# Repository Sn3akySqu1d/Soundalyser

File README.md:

# Description  
Soundalyser is a compact portable sound monitoring device that records, logs and displays ambient noise.  

Key Features:  
5 screens navigatable using a rotary encoder:  
Waveform, sound bar chart, mood screen that compares the current average sound levels to recommended limits, a stats screen that shows number of samples taken, minimum/maximum recorded sound levels and average sound level and a screen that shows details about the SD card.

Data is logged to a csv file on an SD card every 10 minuites so that it can be saved and analysed later. A sample is taken once a second.

A buzzer beeps to alert the user if the sound level gets dangerously loud. (>900 average)

Display autosleeps and is woken by pushing in the rotary encoder.  

I made this project as an easy way to tell if the environment is too loud.

# BOM 
| Component                                       | Link                                                                                                                                               | Price (USD) |
| ----------------------------------------------- | -------------------------------------------------------------------------------------------------------------------------------------------------- | ----------- |
| 0.96 Inch OLED Display Module (SSD1306)         | [https://www.aliexpress.com/item/1005006262908701.html](https://www.aliexpress.com/item/1005006262908701.html)                                     | 3.51        |
| GY-MAX4466 Electret Microphone Amplifier Module | [https://www.aliexpress.com/item/1005006070858246.html](https://www.aliexpress.com/item/1005006070858246.html)                                     | 3.92        |
| RP2040 Seeed XIAO                               | [https://www.aliexpress.com/item/1005003682505451.html](https://www.aliexpress.com/item/1005003682505451.html)                                     | 12.11       |
| Rotary Encoder                                  | [https://www.aliexpress.com/item/1975155185.html](https://www.aliexpress.com/item/1975155185.html)                                                 | 3.62        |
| Buzzer                                          | [https://www.aliexpress.com/item/1005004883467830.html#nav-specification](https://www.aliexpress.com/item/1005004883467830.html#nav-specification) | 3.43        |
| MicroSD Card Reader                             | [https://www.aliexpress.com/item/1005006248599786.html](https://www.aliexpress.com/item/1005006248599786.html)                                     | 2.39        |
| MicroSD Card                                    | [https://www.aliexpress.com/item/1005007118463161.html](https://www.aliexpress.com/item/1005007118463161.html)                                     | 1.99        |
| M3 Screws                                       | [https://www.aliexpress.com/item/32950591394.html](https://www.aliexpress.com/item/32950591394.html)                                               | 4.89        |
| PCB (custom)                                    | [https://jlcpcb.com](https://jlcpcb.com)                                                                                                           | 1.50        |
| Case                                            | Printed with my own 3D printer                                                                                                                     | 0.00        |
 Total: 37.36 usd

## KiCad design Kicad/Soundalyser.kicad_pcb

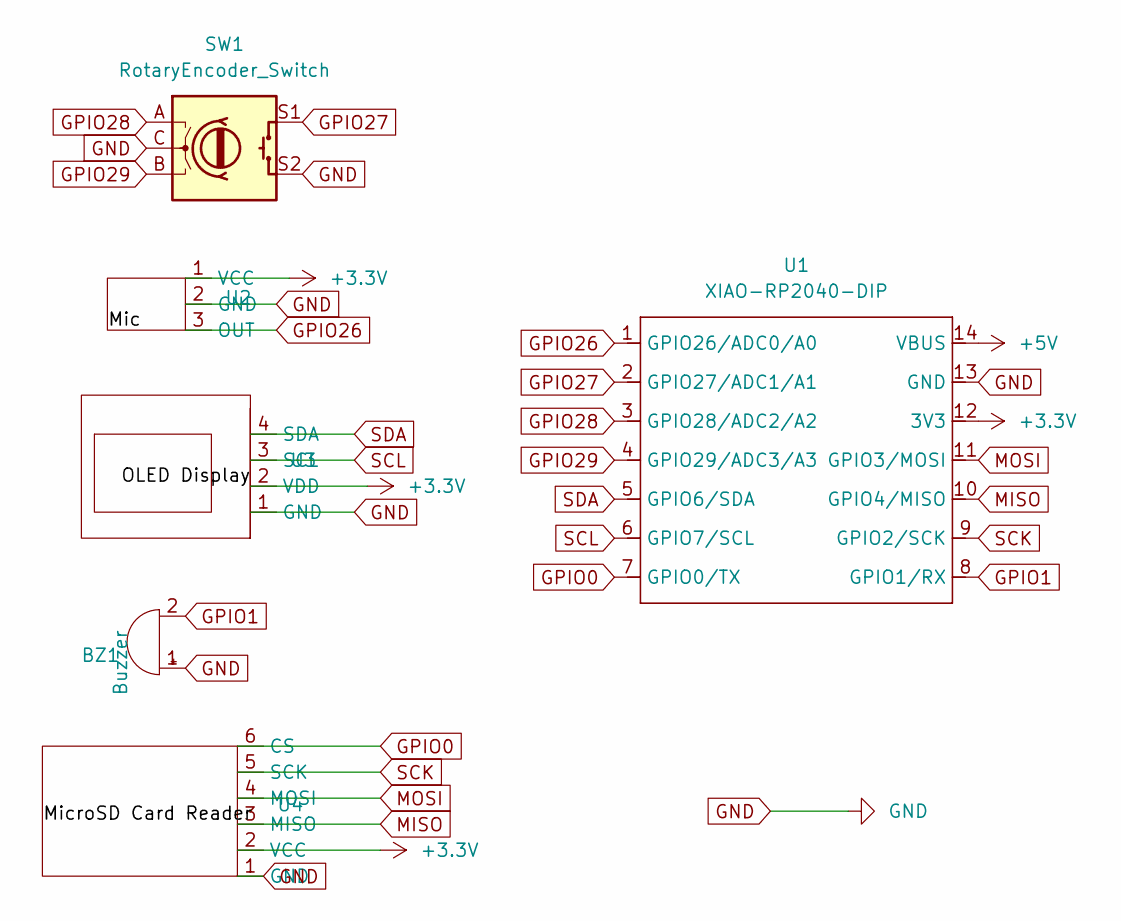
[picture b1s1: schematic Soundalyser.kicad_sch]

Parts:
BZ1: Buzzer; Buzzer_12x9.5RM7.6
SW1: RotaryEncoder_Switch; RotaryEncoder_Alps_EC11E-Switch_Vertical_H20mm
U1: XIAO-RP2040-DIP
U2: GY-MAX4466
U3, U4: Untitled

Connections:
+3.3V: U1.12 (3V3), U2.1 (VCC), U3.2 (VDD), U4.2 (VCC)
+5V: U1.14 (VBUS)
GND: BZ1.1 (+), SW1.C, SW1.S2, U1.13 (GND), U2.2 (GND), U3.1 (GND), U4.1 (GND)
GPIO0: U1.7 (GPIO0/TX), U4.6 (CS)
GPIO1: BZ1.2 (-), U1.8 (GPIO1/RX)
GPIO26: U1.1 (GPIO26/ADC0/A0), U2.3 (OUT)
GPIO27: SW1.S1, U1.2 (GPIO27/ADC1/A1)
GPIO28: SW1.A, U1.3 (GPIO28/ADC2/A2)
GPIO29: SW1.B, U1.4 (GPIO29/ADC3/A3)
MISO: U1.10 (GPIO4/MISO), U4.3 (MISO)
MOSI: U1.11 (GPIO3/MOSI), U4.4 (MOSI)
SCK: U1.9 (GPIO2/SCK), U4.5 (SCK)
SCL: U1.6 (GPIO7/SCL), U3.3 (SCL)
SDA: U1.5 (GPIO6/SDA), U3.4 (SDA)

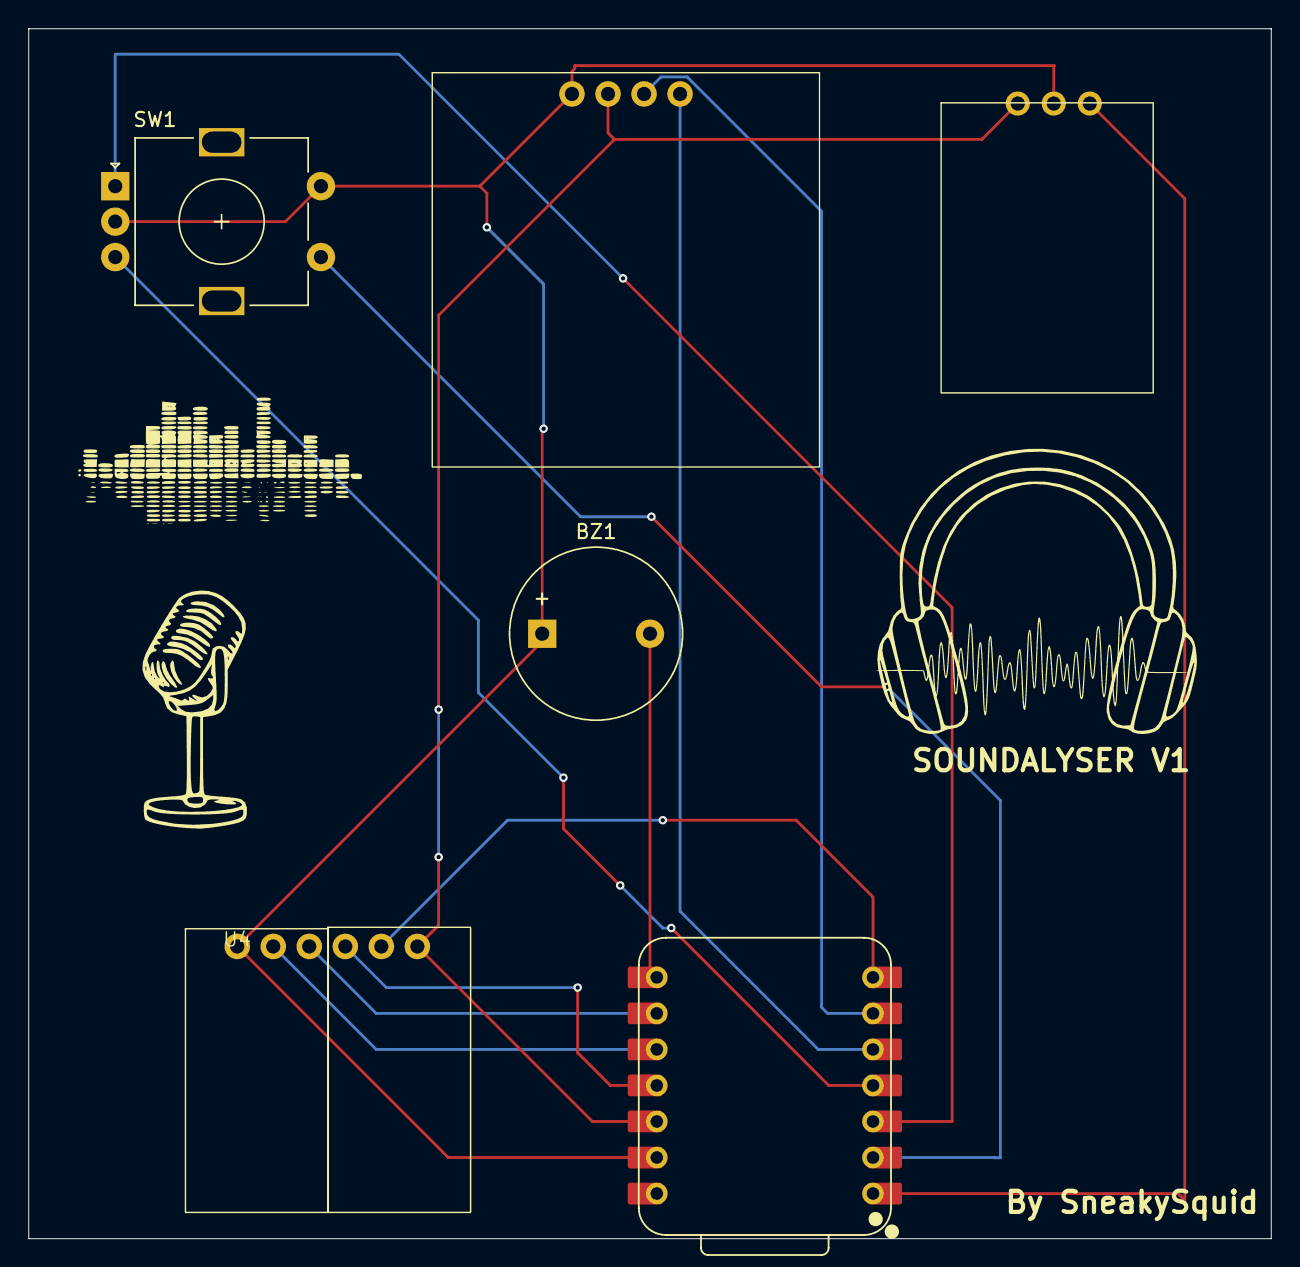
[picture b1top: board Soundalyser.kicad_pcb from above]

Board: 2 copper layers, 87.6 x 85.3 mm, 6 parts (0 on the bottom side), 13 nets.

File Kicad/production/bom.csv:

Designator,Footprint,Quantity,Value,LCSC Part #
BZ1,Buzzer_12x9.5RM7.6,1,Buzzer,
SW1,RotaryEncoder_Alps_EC11E-Switch_Vertical_H20mm,1,RotaryEncoder_Switch,
U1,XIAO-RP2040-DIP,1,XIAO-RP2040-DIP,
U2,GY-MAX4466,1,~,
"U3, U4",Untitled,2,~,

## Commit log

2025-07-09 Upload
2025-07-09 updated microsd card reader
2025-07-17 update journal
2025-07-17 updated journal
2025-07-20 updated firmware after testing on prototype
2025-07-31 updated cad
2025-08-04 build completed
2025-08-04 fixed readme images
2025-08-06 updated read me cad images
